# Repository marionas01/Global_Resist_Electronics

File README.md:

This Repo contains the Schematics and PCB files for the electronic components of the EvolChip.

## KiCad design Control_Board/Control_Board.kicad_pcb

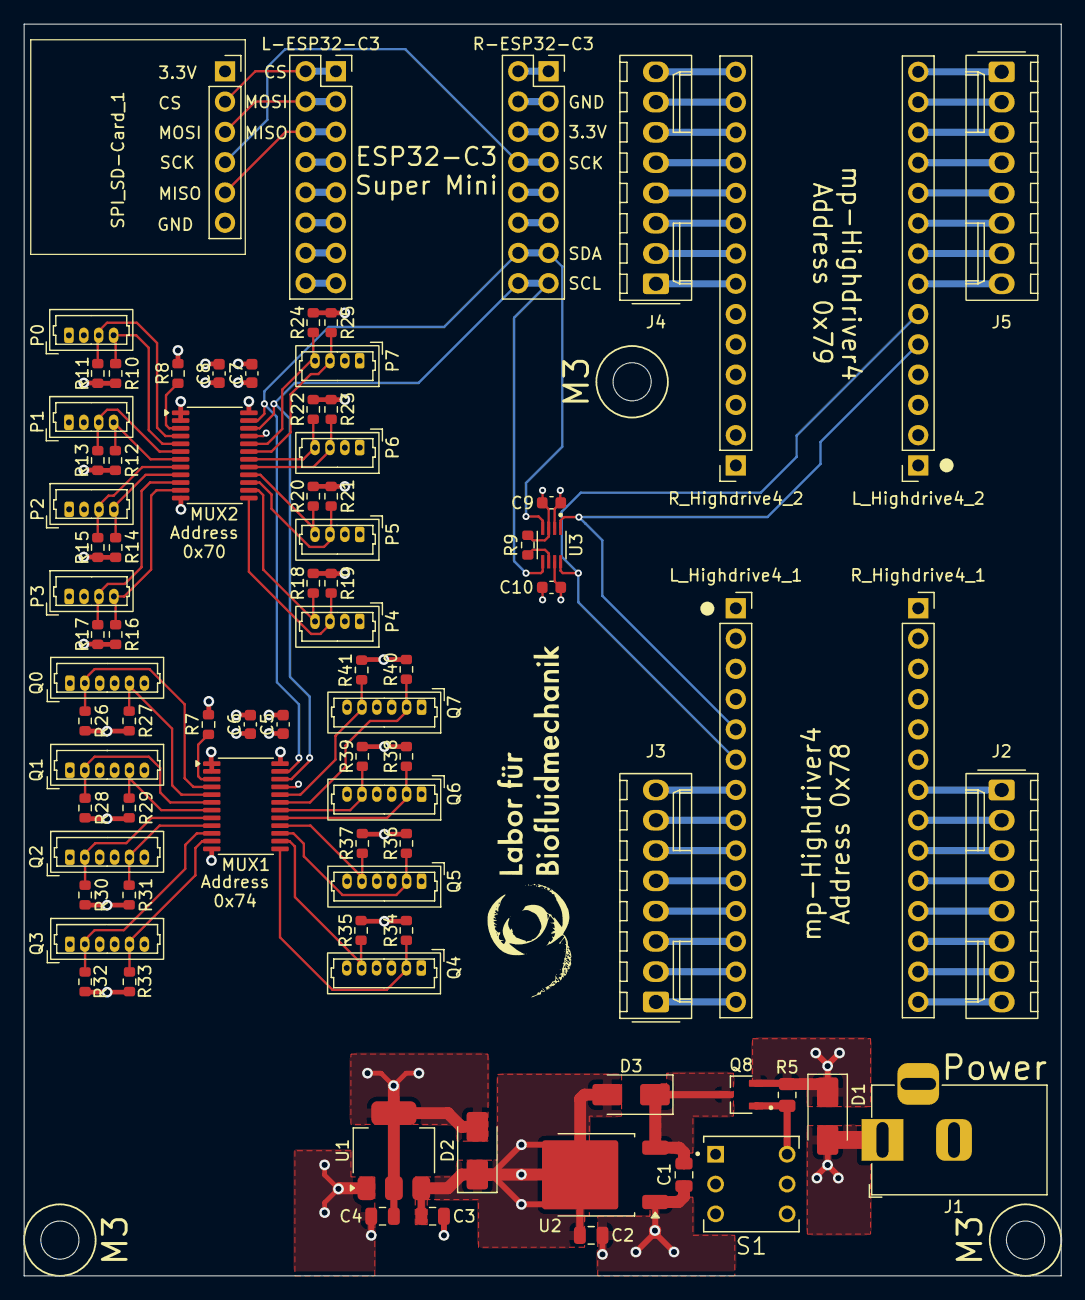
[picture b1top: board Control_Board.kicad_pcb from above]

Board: 4 copper layers, 87.0 x 105.0 mm, 84 parts (0 on the bottom side), 82 nets.

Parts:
C1: 10uF; C_0805_2012Metric
C2: 22uF; C_0805_2012Metric
C3: 1uF; C_0805_2012Metric
C4: 2.2uF; C_0805_2012Metric
C5, C7, C9, C10: 0.1uF; C_0603_1608Metric
C6, C8: 1uF; C_0603_1608Metric
D1, D2, D3: B340A; D_SMA
J1: Barrel_Jack_Switch; BarrelJack_Horizontal
J2, J3, J4, J5: C2982037; Molex_KK-254_AE-6410-08A_1x08_P2.54mm_Vertical
L-ESP32-C3: C30734; PinSocket_2x08_P2.54mm_Vertical
L_Highdrive4_1, L_Highdrive4_2: C2905420; PinSocket_1x14_P2.54mm_Vertical
MUX1, MUX2: TCA9548APWR; TSSOP-24_4.4x7.8mm_P0.65mm
P0, P1, P2, P3, P4, P5, P6, P7: MOLEX 530470410; Molex_PicoBlade_53047-0410_1x04_P1.25mm_Vertical
Q0, Q1, Q2, Q3, Q4, Q5, Q6, Q7: MOLEX 530470610; Molex_PicoBlade_53047-0610_1x06_P1.25mm_Vertical
Q8: AO3407A; SOT95P280X125-3N
R5: 10k; R_0805_2012Metric
R7, R8, R10, R11, R12, R13, R14, R15, R16, R17, R18, R19, R20, R21, R22, R23, R24, R25, R26, R27, R28, R29, R30, R31, R32, R33, R34, R35, R36, R37, R38, R39, R40, R41: 4.7k; R_0603_1608Metric
R9: 10k; R_0603_1608Metric
R-ESP32-C3: C30734; PinSocket_2x08_P2.54mm_Vertical
R_Highdrive4_1, R_Highdrive4_2: C2905420; PinSocket_1x14_P2.54mm_Vertical
S1: TL2285EE; SW_TL2285EE
SPI_SD-Card_1: Conn_01x06; PinSocket_1x06_P2.54mm_Vertical
U1: TLV76133DCY; SOT-223-3_TabPin2
U2: AZ1084CD-5.0TRG1; TO-252-2
U3: TCA9406DCUR; SOP50P310X90-8N

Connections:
+3.3V: C4.1, C5.1, C6.1, C7.1, C8.1, C9.1, D2.2 (A), MUX1.21 (A2), MUX1.24 (VCC), MUX2.24 (VCC), P0.2, P1.2, P2.2, P3.2, P4.2, P5.2, P6.2, P7.2, Q0.3, Q1.3, Q2.3, Q3.3, Q4.3, Q5.3, Q6.3, Q7.3, R7.2, R8.2, R9.1, R10.2, R11.2, R12.2, R13.2, R14.2, R15.2, R16.2, R17.2, R18.2, R19.2, R20.2, R21.2, R22.2, R23.2, R24.2, R25.2, R26.2, R27.2, R28.2, R29.2, R30.2, R31.2, R32.2, R33.2, R34.2, R35.2, R36.2, R37.2, R38.2, R39.2, R40.2, R41.2, R-ESP32-C3.5, R-ESP32-C3.6, SPI_SD-Card_1.1, U1.2 (VO), U3.3 (VCCA)
+5V: C2.1, C3.1, C10.1, D2.1 (K), D3.2 (A), L_Highdrive4_1.2, L_Highdrive4_2.2, L_Highdrive4_2.3, R_Highdrive4_1.1, R_Highdrive4_2.1, U1.3 (VI), U2.2 (VO), U3.7 (VCCB)
+9V: D1.1 (K), Q8.2, R5.2
/CS: L-ESP32-C3.1, L-ESP32-C3.2, SPI_SD-Card_1.2
/MISO: L-ESP32-C3.5, L-ESP32-C3.6, SPI_SD-Card_1.5
/MOSI: L-ESP32-C3.3, L-ESP32-C3.4, SPI_SD-Card_1.3
/PIEZO11+_1: J2.7, R_Highdrive4_1.13
/PIEZO11+_2: J4.7, R_Highdrive4_2.13
/PIEZO11-_1: J2.8, R_Highdrive4_1.14
/PIEZO11-_2: J4.8, R_Highdrive4_2.14
/PIEZO12+_1: J2.6, R_Highdrive4_1.12
/PIEZO12+_2: J4.6, R_Highdrive4_2.12
/PIEZO12-_1: J2.5, R_Highdrive4_1.11
/PIEZO12-_2: J4.5, R_Highdrive4_2.11
/PIEZO21+_1: J2.3, R_Highdrive4_1.9
/PIEZO21+_2: J4.3, R_Highdrive4_2.9
/PIEZO21-_1: J2.4, R_Highdrive4_1.10
/PIEZO21-_2: J4.4, R_Highdrive4_2.10
/PIEZO22+_1: J2.2, R_Highdrive4_1.8
/PIEZO22+_2: J4.2, R_Highdrive4_2.8
/PIEZO22-_1: J2.1, R_Highdrive4_1.7
/PIEZO22-_2: J4.1, R_Highdrive4_2.7
/PIEZO31+_1: J3.7, L_Highdrive4_1.8
/PIEZO31+_2: J5.7, L_Highdrive4_2.8
/PIEZO31-_1: J3.8, L_Highdrive4_1.7
/PIEZO31-_2: J5.8, L_Highdrive4_2.7
/PIEZO32+_1: J3.6, L_Highdrive4_1.9
/PIEZO32+_2: J5.6, L_Highdrive4_2.9
/PIEZO32-_1: J3.5, L_Highdrive4_1.10
/PIEZO32-_2: J5.5, L_Highdrive4_2.10
/PIEZO41+_1: J3.3, L_Highdrive4_1.12
/PIEZO41+_2: J5.3, L_Highdrive4_2.12
/PIEZO41-_1: J3.4, L_Highdrive4_1.11
/PIEZO41-_2: J5.4, L_Highdrive4_2.11
/PIEZO42+_1: J3.2, L_Highdrive4_1.13
/PIEZO42+_2: J5.2, L_Highdrive4_2.13
/PIEZO42-_1: J3.1, L_Highdrive4_1.14
/PIEZO42-_2: J5.1, L_Highdrive4_2.14
/SC0_P: MUX2.5 (SC0), P0.4, R10.1
/SC0_Q: MUX1.5 (SC0), Q0.5, R27.1
/SC1_P: MUX2.7 (SC1), P1.4, R12.1
/SC1_Q: MUX1.7 (SC1), Q1.5, R29.1
/SC2_P: MUX2.9 (SC2), P2.4, R14.1
/SC2_Q: MUX1.9 (SC2), Q2.5, R31.1
/SC3_P: MUX2.11 (SC3), P3.4, R16.1
/SC3_Q: MUX1.11 (SC3), Q3.5, R33.1
/SC4_P: MUX2.14 (SC4), P4.4, R18.1
/SC4_Q: MUX1.14 (SC4), Q4.5, R35.1
/SC5_P: MUX2.16 (SC5), P5.4, R20.1
/SC5_Q: MUX1.16 (SC5), Q5.5, R37.1
/SC6_P: MUX2.18 (SC6), P6.4, R22.1
/SC6_Q: MUX1.18 (SC6), Q6.5, R39.1
/SC7_P: MUX2.20 (SC7), P7.4, R24.1
/SC7_Q: MUX1.20 (SC7), Q7.5, R41.1
/SCK: R-ESP32-C3.7, R-ESP32-C3.8, SPI_SD-Card_1.4
/SCL_3.3V: MUX1.22 (SCL), MUX2.22 (SCL), R-ESP32-C3.15, R-ESP32-C3.16, U3.5 (SCL_A)
/SCL_5V: L_Highdrive4_1.6, L_Highdrive4_2.6, U3.8 (SCL_B)
/SD0_P: MUX2.4 (SD0), P0.3, R11.1
/SD0_Q: MUX1.4 (SD0), Q0.2, R26.1
/SD1_P: MUX2.6 (SD1), P1.3, R13.1
/SD1_Q: MUX1.6 (SD1), Q1.2, R28.1
/SD2_P: MUX2.8 (SD2), P2.3, R15.1
/SD2_Q: MUX1.8 (SD2), Q2.2, R30.1
/SD3_P: MUX2.10 (SD3), P3.3, R17.1
/SD3_Q: MUX1.10 (SD3), Q3.2, R32.1
/SD4_P: MUX2.13 (SD4), P4.3, R19.1
/SD4_Q: MUX1.13 (SD4), Q4.2, R34.1
/SD5_P: MUX2.15 (SD5), P5.3, R21.1
/SD5_Q: MUX1.15 (SD5), Q5.2, R36.1
/SD6_P: MUX2.17 (SD6), P6.3, R23.1
/SD6_Q: MUX1.17 (SD6), Q6.2, R38.1
/SD7_P: MUX2.19 (SD7), P7.3, R25.1
/SD7_Q: MUX1.19 (SD7), Q7.2, R40.1
/SDA_3.3V: MUX1.23 (SDA), MUX2.23 (SDA), R-ESP32-C3.13, R-ESP32-C3.14, U3.4 (SDA_A)
/SDA_5V: L_Highdrive4_1.5, L_Highdrive4_2.5, U3.1 (SDA_B)
GNDREF: C1.2, C2.2, C3.2, C4.2, C5.2, C6.2, C7.2, C8.2, C9.2, C10.2, J1.2, J1.3, L_Highdrive4_1.1, L_Highdrive4_1.3, L_Highdrive4_1.4, L_Highdrive4_2.1, L_Highdrive4_2.4, MUX1.1 (A0), MUX1.2 (A1), MUX1.12 (GND), MUX2.1 (A0), MUX2.2 (A1), MUX2.12 (GND), MUX2.21 (A2), P0.1, P1.1, P2.1, P3.1, P4.1, P5.1, P6.1, P7.1, Q0.1, Q0.4, Q0.6, Q1.1, Q1.4, Q1.6, Q2.1, Q2.4, Q2.6, Q3.1, Q3.4, Q3.6, Q4.1, Q4.4, Q4.6, Q5.1, Q5.4, Q5.6, Q6.1, Q6.4, Q6.6, Q7.1, Q7.4, Q7.6, R-ESP32-C3.3, R-ESP32-C3.4, R_Highdrive4_1.2, R_Highdrive4_2.2, S1.5, SPI_SD-Card_1.6, U1.1 (GND), U2.1 (GND), U3.2 (GND)
unnamed: D1.2 (A), J1.1
unnamed: C1.1, D3.1 (K), Q8.3, U2.3 (VI)
unnamed: MUX1.3 (~RESET), R7.1
unnamed: MUX2.3 (~RESET), R8.1
unnamed: Q8.1, R5.1, S1.4
unnamed: R9.2, U3.6 (OE)

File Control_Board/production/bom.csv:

Designator,Footprint,Quantity,Value,LCSC Part #
C1,0805,1,10uF,
"C10, C5, C7, C9",0603,4,0.1uF,
C2,0805,1,22uF,
C3,0805,1,1uF,
C4,0805,1,2.2uF,
"C6, C8",0603,2,1uF,
"D1, D2, D3",D_SMA,3,B340A,
J1,BarrelJack_Horizontal,1,Barrel_Jack_Switch,
"J2, J3, J4, J5",Molex_KK-254_AE-6410-08A_1x08_P2.54mm_Vertical,4,C2982037,
"L-ESP32-C3, R-ESP32-C3",PinSocket_2x08_P2.54mm_Vertical,2,C30734,
"L_HIGHDRIVE4_1, L_HIGHDRIVE4_2, R_HIGHDRIVE4_1, R_HIGHDRIVE4_2",PinSocket_1x14_P2.54mm_Vertical,4,C2905420,
"MUX1, MUX2",TSSOP-24_4.4x7.8mm_P0.65mm,2,TCA9548APWR,
"P0, P1, P2, P3, P4, P5, P6, P7",Molex_PicoBlade_53047-0410_1x04_P1.25mm_Vertical,8,MOLEX 530470410,
"Q0, Q1, Q2, Q3, Q4, Q5, Q6, Q7",Molex_PicoBlade_53047-0610_1x06_P1.25mm_Vertical,8,MOLEX 530470610,
Q8,SOT95P280X125-3N,1,AO3407A,
"R10, R11, R12, R13, R14, R15, R16, R17, R18, R19, R20, R21, R22, R23, R24, R25, R26, R27, R28, R29, R30, R31, R32, R33, R34, R35, R36, R37, R38, R39, R40, R41, R7, R8",0603,34,4.7k,
R5,0805,1,10k,
R9,0603,1,10k,
S1,SW_TL2285EE,1,TL2285EE,
SPI_SD-CARD_1,PinSocket_1x06_P2.54mm_Vertical,1,Conn_01x06,
U1,SOT-223-3_TabPin2,1,TLV76133DCY,
U2,TO-252-2,1,AZ1084CD-5.0TRG1,
U3,SOP50P310X90-8N,1,TCA9406DCUR,

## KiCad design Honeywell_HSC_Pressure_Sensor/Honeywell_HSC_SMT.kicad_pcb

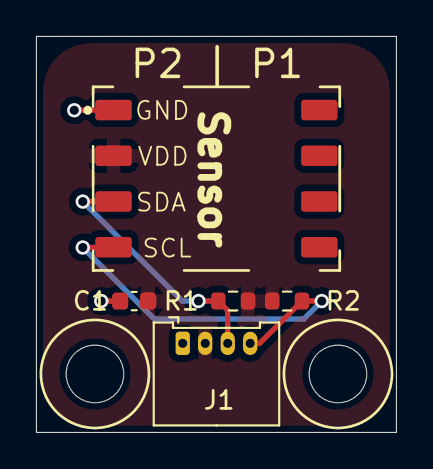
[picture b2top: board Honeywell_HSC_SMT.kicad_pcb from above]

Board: 2 copper layers, 20.0 x 22.0 mm, 5 parts (0 on the bottom side), 4 nets.

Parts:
C1: 0.1uF; C_0603_1608Metric
J1: Conn_01x04; Molex_PicoBlade_53048-0410_1x04_P1.25mm_Horizontal
R1, R2: 10k; R_0603_1608Metric
Sensor: Honeywell_HSC_SMT

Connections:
/GND: C1.1, J1.1, Sensor.1 (GND)
/SCL: J1.4, R2.2, Sensor.4 (SCL)
/SDA: J1.3, R1.2, Sensor.3 (SDA)
/VDD: C1.2, J1.2, R1.1, R2.1, Sensor.2 (VDD)

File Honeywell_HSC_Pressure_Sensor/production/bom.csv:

Designator,Footprint,Quantity,Value,LCSC Part #
C1,0603,1,0.1uF,
J1,Molex_PicoBlade_53048-0410_1x04_P1.25mm_Horizontal,1,Conn_01x04,
"R1, R2",0603,2,10k,
SENSOR,Honeywell_HSC_SMT,1,Honeywell_HSC_SMT,

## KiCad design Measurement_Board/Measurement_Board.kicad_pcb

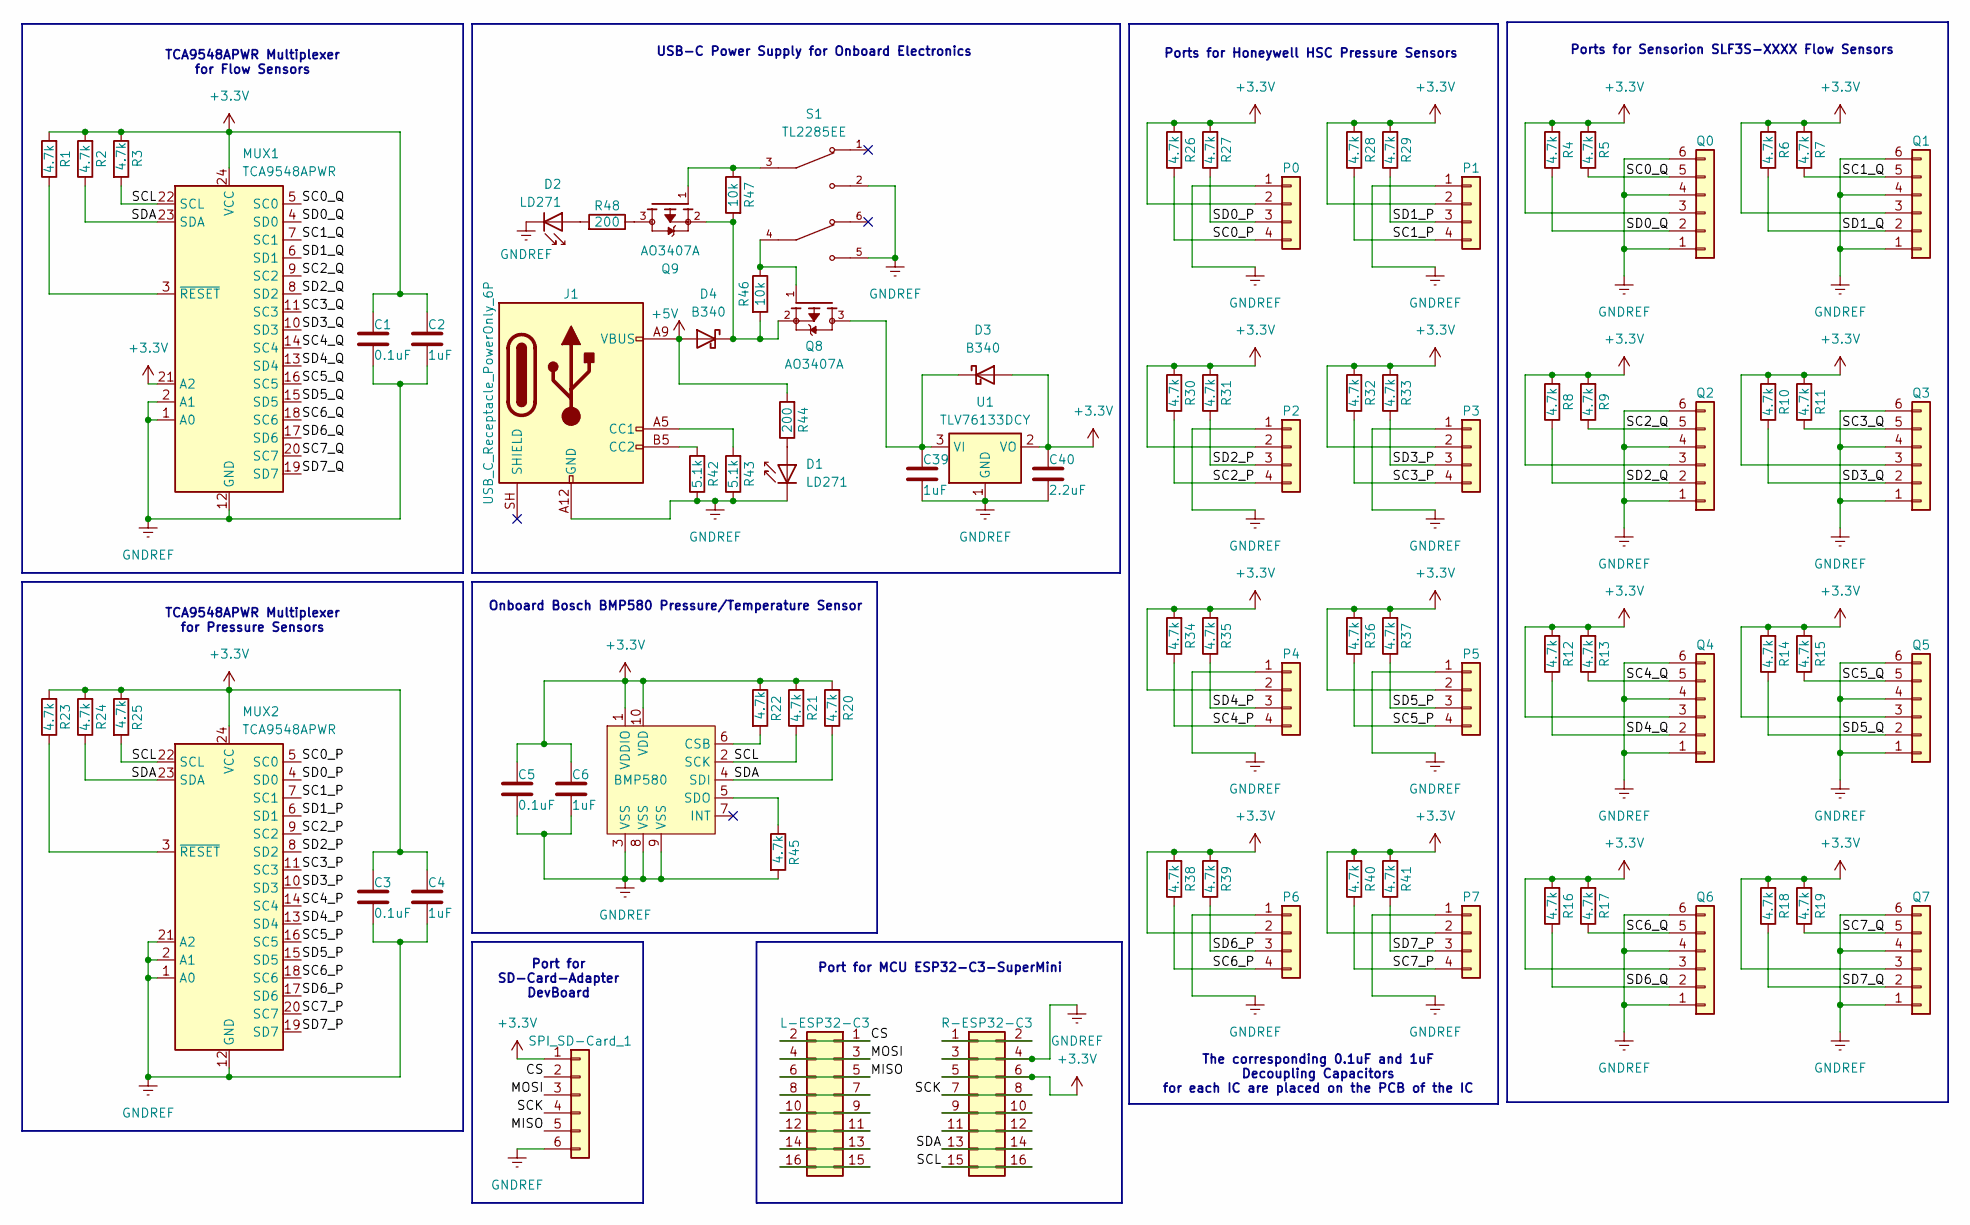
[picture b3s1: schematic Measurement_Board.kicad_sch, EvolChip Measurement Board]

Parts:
BMP580: BMP580
C1, C3, C5: 0.1uF; C_0603_1608Metric
C2, C4, C6: 1uF; C_0603_1608Metric
C39: 1uF; C_0805_2012Metric
C40: 2.2uF; C_0805_2012Metric
D1, D2: LD271; D_0603_1608Metric
D3, D4: B340; D_SMA
J1: USB_C_Receptacle_PowerOnly_6P; USB_C_Receptacle_GCT_USB4125-xx-x-0190_6P_TopMnt_Horizontal
L-ESP32-C3: Conn_02x08_Odd_Even; PinSocket_2x08_P2.54mm_Vertical
MUX1, MUX2: TCA9548APWR; TSSOP-24_4.4x7.8mm_P0.65mm
P0, P1, P2, P3, P4, P5, P6, P7: Conn_01x04; Molex_PicoBlade_53047-0410_1x04_P1.25mm_Vertical
Q0, Q1, Q2, Q3, Q4, Q5, Q6, Q7: Conn_01x06; Molex_PicoBlade_53047-0610_1x06_P1.25mm_Vertical
Q8, Q9: AO3407A; SOT95P280X125-3N; PARTREV 5
R1, R2, R3, R4, R5, R6, R7, R8, R9, R10, R11, R12, R13, R14, R15, R16, R17, R18, R19, R20, R21, R22, R23, R24, R25, R26, R27, R28, R29, R30, R31, R32, R33, R34, R35, R36, R37, R38, R39, R40, R41, R45: 4.7k; R_0603_1608Metric
R42, R43: 5.1k; R_0805_2012Metric
R44, R48: 200; R_0603_1608Metric
R46, R47: 10k; R_0805_2012Metric
R-ESP32-C3: Conn_02x08_Odd_Even; PinSocket_2x08_P2.54mm_Vertical
S1: TL2285EE; SW_TL2285EE; PARTREV B
SPI_SD-Card_1: Conn_01x06; PinSocket_1x06_P2.54mm_Vertical
U1: TLV76133DCY; SOT-223-3_TabPin2

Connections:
+3.3V: BMP580.1 (VDDIO), BMP580.10 (VDD), C1.1, C2.1, C3.1, C4.1, C5.1, C6.1, C40.1, D3.2 (A), MUX1.21 (A2), MUX1.24 (VCC), MUX2.24 (VCC), P0.2, P1.2, P2.2, P3.2, P4.2, P5.2, P6.2, P7.2, Q0.3, Q1.3, Q2.3, Q3.3, Q4.3, Q5.3, Q6.3, Q7.3, R1.2, R2.2, R3.1, R4.2, R5.2, R6.2, R7.2, R8.2, R9.2, R10.2, R11.2, R12.2, R13.2, R14.2, R15.2, R16.2, R17.2, R18.2, R19.2, R20.2, R21.2, R22.1, R23.2, R24.2, R25.1, R26.2, R27.2, R28.2, R29.2, R30.2, R31.2, R32.2, R33.2, R34.2, R35.2, R36.2, R37.2, R38.2, R39.2, R40.2, R41.2, R-ESP32-C3.5, R-ESP32-C3.6, SPI_SD-Card_1.1, U1.2 (VO)
+5V: D4.2 (A), J1.A9 (VBUS), J1.B9 (VBUS), R44.2
/CS: L-ESP32-C3.1, L-ESP32-C3.2, SPI_SD-Card_1.2
/MISO: L-ESP32-C3.5, L-ESP32-C3.6, SPI_SD-Card_1.5
/MOSI: L-ESP32-C3.3, L-ESP32-C3.4, SPI_SD-Card_1.3
/SC0_P: MUX2.5 (SC0), P0.4, R26.1
/SC0_Q: MUX1.5 (SC0), Q0.5, R5.1
/SC1_P: MUX2.7 (SC1), P1.4, R28.1
/SC1_Q: MUX1.7 (SC1), Q1.5, R7.1
/SC2_P: MUX2.9 (SC2), P2.4, R30.1
/SC2_Q: MUX1.9 (SC2), Q2.5, R9.1
/SC3_P: MUX2.11 (SC3), P3.4, R32.1
/SC3_Q: MUX1.11 (SC3), Q3.5, R11.1
/SC4_P: MUX2.14 (SC4), P4.4, R34.1
/SC4_Q: MUX1.14 (SC4), Q4.5, R13.1
/SC5_P: MUX2.16 (SC5), P5.4, R36.1
/SC5_Q: MUX1.16 (SC5), Q5.5, R15.1
/SC6_P: MUX2.18 (SC6), P6.4, R38.1
/SC6_Q: MUX1.18 (SC6), Q6.5, R17.1
/SC7_P: MUX2.20 (SC7), P7.4, R40.1
/SC7_Q: MUX1.20 (SC7), Q7.5, R19.1
/SCK: R-ESP32-C3.7, R-ESP32-C3.8, SPI_SD-Card_1.4
/SCL: BMP580.2 (SCK), MUX1.22 (SCL), MUX2.22 (SCL), R3.2, R21.1, R25.2, R-ESP32-C3.15, R-ESP32-C3.16
/SD0_P: MUX2.4 (SD0), P0.3, R27.1
/SD0_Q: MUX1.4 (SD0), Q0.2, R4.1
/SD1_P: MUX2.6 (SD1), P1.3, R29.1
/SD1_Q: MUX1.6 (SD1), Q1.2, R6.1
/SD2_P: MUX2.8 (SD2), P2.3, R31.1
/SD2_Q: MUX1.8 (SD2), Q2.2, R8.1
/SD3_P: MUX2.10 (SD3), P3.3, R33.1
/SD3_Q: MUX1.10 (SD3), Q3.2, R10.1
/SD4_P: MUX2.13 (SD4), P4.3, R35.1
/SD4_Q: MUX1.13 (SD4), Q4.2, R12.1
/SD5_P: MUX2.15 (SD5), P5.3, R37.1
/SD5_Q: MUX1.15 (SD5), Q5.2, R14.1
/SD6_P: MUX2.17 (SD6), P6.3, R39.1
/SD6_Q: MUX1.17 (SD6), Q6.2, R16.1
/SD7_P: MUX2.19 (SD7), P7.3, R41.1
/SD7_Q: MUX1.19 (SD7), Q7.2, R18.1
/SDA: BMP580.4 (SDI), MUX1.23 (SDA), MUX2.23 (SDA), R2.1, R20.1, R24.1, R-ESP32-C3.13, R-ESP32-C3.14
GNDREF: BMP580.3 (VSS), BMP580.8 (VSS), BMP580.9 (VSS), C1.2, C2.2, C3.2, C4.2, C5.2, C6.2, C39.2, C40.2, D1.1 (K), D2.1 (K), J1.A12 (GND), J1.B12 (GND), MUX1.1 (A0), MUX1.2 (A1), MUX1.12 (GND), MUX2.1 (A0), MUX2.2 (A1), MUX2.12 (GND), MUX2.21 (A2), P0.1, P1.1, P2.1, P3.1, P4.1, P5.1, P6.1, P7.1, Q0.1, Q0.4, Q0.6, Q1.1, Q1.4, Q1.6, Q2.1, Q2.4, Q2.6, Q3.1, Q3.4, Q3.6, Q4.1, Q4.4, Q4.6, Q5.1, Q5.4, Q5.6, Q6.1, Q6.4, Q6.6, Q7.1, Q7.4, Q7.6, R42.1, R43.1, R45.2, R-ESP32-C3.3, R-ESP32-C3.4, S1.2, S1.5, SPI_SD-Card_1.6, U1.1 (GND)
unnamed: BMP580.6 (CSB), R22.2
unnamed: BMP580.5 (SDO), R45.1
unnamed: D1.2 (A), R44.1
unnamed: D2.2 (A), R48.2
unnamed: C39.1, D3.1 (K), Q8.3, U1.3 (VI)
unnamed: D4.1 (K), Q8.2, Q9.2, R46.2, R47.2
unnamed: J1.A5 (CC1), R43.2
unnamed: J1.B5 (CC2), R42.2
unnamed: L-ESP32-C3.7, L-ESP32-C3.8
unnamed: L-ESP32-C3.9, L-ESP32-C3.10
unnamed: L-ESP32-C3.11, L-ESP32-C3.12
unnamed: L-ESP32-C3.13, L-ESP32-C3.14
unnamed: L-ESP32-C3.15, L-ESP32-C3.16
unnamed: MUX1.3 (~RESET), R1.1
unnamed: MUX2.3 (~RESET), R23.1
unnamed: Q8.1, R46.1, S1.4
unnamed: Q9.1, R47.1, S1.3
unnamed: Q9.3, R48.1
unnamed: R-ESP32-C3.1, R-ESP32-C3.2
unnamed: R-ESP32-C3.9, R-ESP32-C3.10
unnamed: R-ESP32-C3.11, R-ESP32-C3.12

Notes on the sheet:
Port for MCU ESP32-C3-SuperMini
The corresponding 0.1uF and 1uF Decoupling Capacitors for each IC are placed on the PCB of the IC
Onboard Bosch BMP580 Pressure/Temperature Sensor
USB-C Power Supply for Onboard Electronics
TCA9548APWR Multiplexer for Flow Sensors
TCA9548APWR Multiplexer for Pressure Sensors
Ports for Sensorion SLF3S-XXXX Flow Sensors
Ports for Honeywell HSC Pressure Sensors
Port for SD-Card-Adapter DevBoard

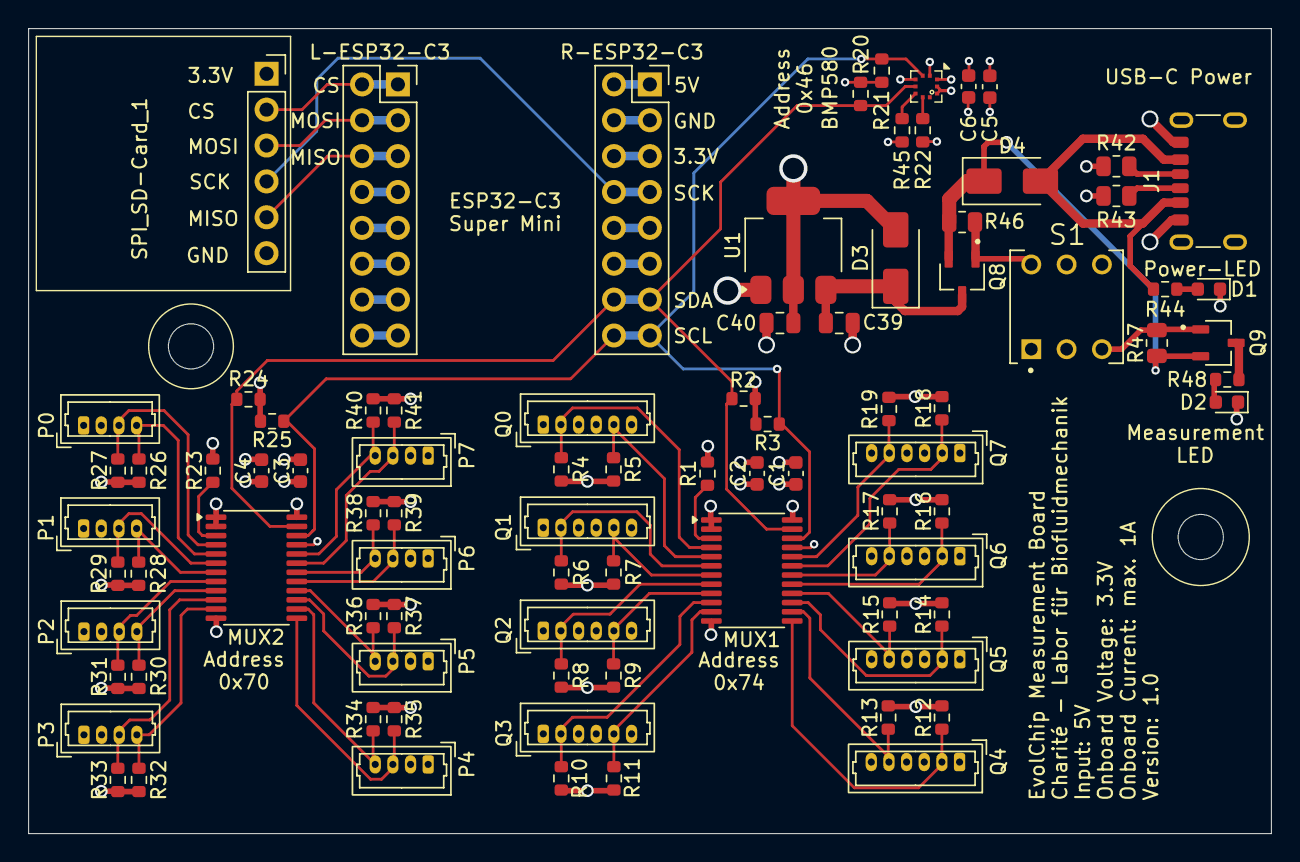
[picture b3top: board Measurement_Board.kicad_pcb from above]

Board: 4 copper layers, 88.0 x 57.0 mm, 87 parts (0 on the bottom side), 62 nets.

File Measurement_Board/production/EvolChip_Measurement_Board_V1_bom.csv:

Designator,Footprint,Quantity,Value,LCSC Part #
BMP580,BMP580,1,~,
"C1, C3, C5",0603,3,0.1uF,
"C2, C4, C6",0603,3,1uF,
C39,0805,1,1uF,
C40,0805,1,2.2uF,
"D1, D2",0603,2,LD271,
"D3, D4",D_SMA,2,B340,
J1,USB_C_Receptacle_GCT_USB4125-xx-x-0190_6P_TopMnt_Horizontal,1,USB_C_Receptacle_PowerOnly_6P,
"L-ESP32-C3, R-ESP32-C3",PinSocket_2x08_P2.54mm_Vertical,2,Conn_02x08_Odd_Even,
"MUX1, MUX2",TSSOP-24_4.4x7.8mm_P0.65mm,2,TCA9548APWR,
"P0, P1, P2, P3, P4, P5, P6, P7",Molex_PicoBlade_53047-0410_1x04_P1.25mm_Vertical,8,Conn_01x04,
"Q0, Q1, Q2, Q3, Q4, Q5, Q6, Q7",Molex_PicoBlade_53047-0610_1x06_P1.25mm_Vertical,8,Conn_01x06,
"Q8, Q9",SOT95P280X125-3N,2,AO3407A,
"R1, R10, R11, R12, R13, R14, R15, R16, R17, R18, R19, R2, R20, R21, R22, R23, R24, R25, R26, R27, R28, R29, R3, R30, R31, R32, R33, R34, R35, R36, R37, R38, R39, R4, R40, R41, R45, R5, R6, R7, R8, R9",0603,42,4.7k,
"R42, R43",0805,2,5.1k,
"R44, R48",0603,2,200,
"R46, R47",0805,2,10k,
S1,SW_TL2285EE,1,TL2285EE,
SPI_SD-CARD_1,PinSocket_1x06_P2.54mm_Vertical,1,Conn_01x06,
U1,SOT-223-3_TabPin2,1,TLV76133DCY,
